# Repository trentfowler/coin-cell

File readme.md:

# Coin cell battery backup

**Description:** 5V barrel jack/wall powered circuit with fail over to coin cell backup battery if wall power is disconnected.

**Part List:**
  - TPS61222 (5v Boost/Regulator IC)
  - NC7SZ14 (Schmitt Inverter IC)
  - CR2032 Battery
  - DC Barrel Jack
  - Schottky Diodes (2x)
  - Resistor (1x 10K)
  - Capacitors (1x 100-500uF, 2x 10uF)
  - 4.7uH Inductor
  - 5V Wall Supply

**References:**
  - https://www.digikey.com/short/pfc1m9
  - https://www.youtube.com/watch?v=pqhWlDj8nHc

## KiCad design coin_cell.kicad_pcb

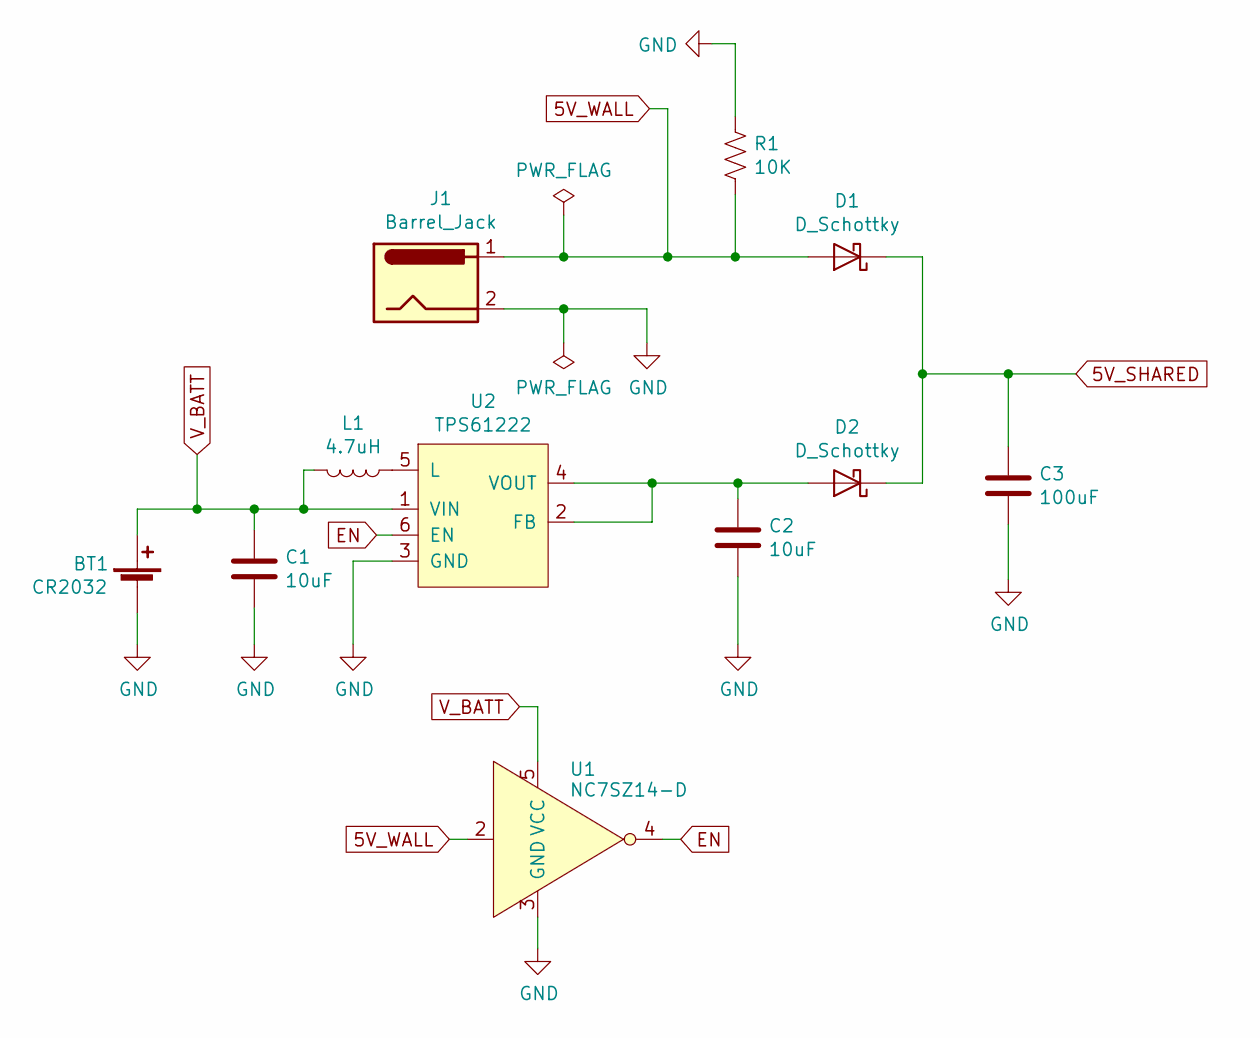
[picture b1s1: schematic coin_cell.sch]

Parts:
BT1: CR2032; S8211R
C1, C2: 10uF; Capacitor_0805_2012Metric_Pad1.15x1.40mm_HandSolder
C3: 100uF; Capacitor_0805_2012Metric_Pad1.15x1.40mm_HandSolder
D1, D2: D_Schottky; Diode_0805_2012Metric_Pad1.15x1.40mm_HandSolder
J1: Barrel_Jack; Barrel_Jack_Small_Hole_Type_5.5mmODx2.1mmID_PJ-102A
L1: 4.7uH; L_10.4x10.4_H4.8
R1: 10K; Resistor_0805_2012Metric_Pad1.15x1.40mm_HandSolder
U1: NC7SZ14-D; SOT-353_SC-70-5_Handsoldering
U2: TPS61222; SOT-363_SC-70-6_Handsoldering

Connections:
5V_SHARED: C3.1, D1.1 (K), D2.1 (K)
5V_WALL: D1.2 (A), J1.1, R1.2, U1.2
EN: U1.4, U2.6 (EN)
GND: BT1.2 (-), C1.2, C2.2, C3.2, J1.2, R1.1, U1.3 (GND), U2.3 (GND)
unnamed: C2.1, D2.2 (A), U2.2 (FB), U2.4 (VOUT)
unnamed: L1.1, U2.5 (L)
V_BATT: BT1.1 (+), C1.1, J1.3, L1.2, U1.5 (VCC), U2.1 (VIN)

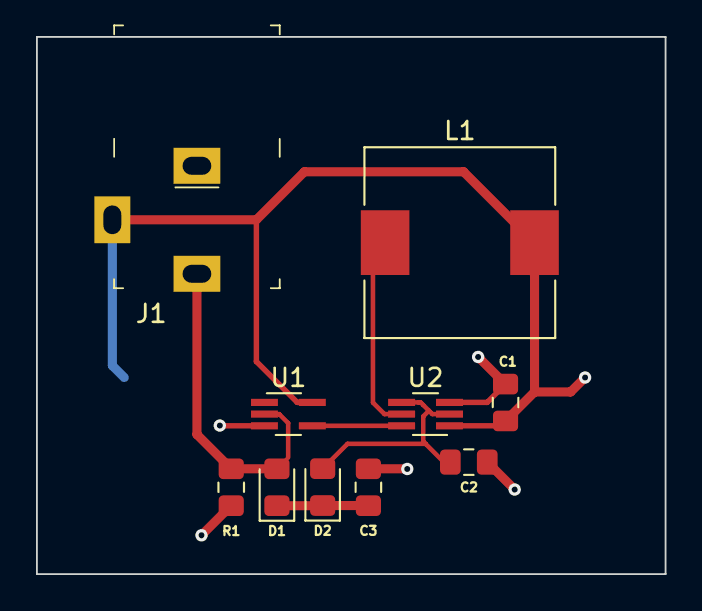
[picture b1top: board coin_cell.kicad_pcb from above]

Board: 2 copper layers, 34.9 x 29.8 mm, 11 parts (1 on the bottom side), 7 nets.

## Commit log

2019-09-09 Added sc-70-5 footprint and sot23-5 footprint
    - assigned footprints to symbols
2019-09-09 Generate net list
    - Open pcbnew and spread components
2019-09-09 pcbnew component placement
2019-09-11 Moved footprints to project lib to remove external dependency req
2019-09-11 Added reference pcb layout
2019-09-11 Adjusted clearances and trace widths
2019-09-11 Moved component labels to improve readability
2019-09-12 Flipped S8211R 180 degrees and re-ran traces
2019-09-13 Increase edge cut thickness to 4 mil
2019-09-13 Add 3d render to readme and moved images to img folder
2019-09-13 Crop 3d render
